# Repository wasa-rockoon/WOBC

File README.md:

View this project on [CADLAB.io](https://cadlab.io/project/27502). 

# WOBC

WOBCは，WASAロケットプロジェクトにおける電装関連の共通基盤を確立することを目的としたプロジェクトである．
開発した回路や基板の設計情報，プログラムといった資産を再利用しやすい形で整備することで，
開発スピードを向上させるとともに引き継ぎや教育を効率的に行えるようにする．

# 用語

## ユニット

単独で動作する，システムの基本単位．例：ロケット電装，CanSat電装，地上局

1つ以上のモジュールから構成される．

## モジュール

コンポーネントを一枚の基板上に配置した，物理的な単位．例：地上局モジュール，通信モジュール

モジュールには必ずマイコンが含まれ，コンポーネントを制御する．
ユニットを構成するモジュール間はバスで接続される．

## コンポーネント

ユニットを構成する，意味のある一つの機能単位．例：電源管理，姿勢決定，モーター駆動

ハードウェアおよびプログラムはコンポーネント単位で開発する．

## パケット

ユニットやコンポーネント間でやり取りするデータの形式．
詳しくは[WCPP](https://github.com/wasa-rockoon/WCPP)を参照．

# 開発

モジュールやコンポーネントは，全てこのリポジトリに格納する（Monorepoスタイル）．

## Gitの運用

- 開発者ごとに，`develop/your_name` ブランチを作成する．
- 全体に反映したい変更ができたらPull Requestを作成し，責任者にレビューを依頼する．
- コンポーネントおよびモジュール作成の際は自分のブランチとは別に，`feature/CompornentOrModule_name`ブランチを作成する．
- コンポーネント・モジュールが完成したらPull Requestを作成し，責任者にレビューを依頼する．
- 責任者は変更をレビューし，問題なければ`main`ブランチにマージする．（回路・基板のレビューには[CADLAB.io](https://cadlab.io/project/27502)を使うと便利)

## Github Copilotの学生無料

昨今コーディング作業に`AI Agent`の活用が主流になってきていると思います．ただ無料枠で利用していてもすぐトークンを使い切ってしまったり，選べるモデルが少なかったりと不便なことが多いかと思います．そこで個人的にはGithub Copilotの学生無料を利用することを推奨しています．導入方法については`ドキュメント`にあるリンクから参照してください．

## 作業ログ

`Github Copilot`の利用にあわせて，作業ログを作ることを習慣化してほしいと思います．おもにコーディング作業についてですが，

- 前にも同じようなエラーが出てたけど，どうやって解消したんだっけとか
- 過去にも似たようなもの作ってたらしいけど，資料が残っていないとか

色々と引継ぎが上手くいっていないような事象を見かけます．非常にもったいないというか二度手間なことが多いので，ちゃんとノウハウを蓄積できるようにしましょう．

具体的には `docs`のフォルダに`env:`毎でフォルダを作りその中で[template](docs/template.md)を参考にしてAIに作らせてください．タスク毎に作るのが良いかと思います．

# ドキュメント

- [develop](docs/develop.md): 詳細な開発の手順
- [kicad](docs/kicad.md): KiCADを用いた回路・基板設計マニュアル
- [github-copilot](docs/github-copilot.md): Github Copilotの導入マニュアル
- [components](docs/components.md): コンポーネントとその機能，インターフェースの一覧
- [modules](docs/modules.md): モジュールとその機能，構成コンポーネントの一覧
- [unit](docs/unit.md): ユニット一覧
- [library](docs/library.md): WOBCライブラリの使い方

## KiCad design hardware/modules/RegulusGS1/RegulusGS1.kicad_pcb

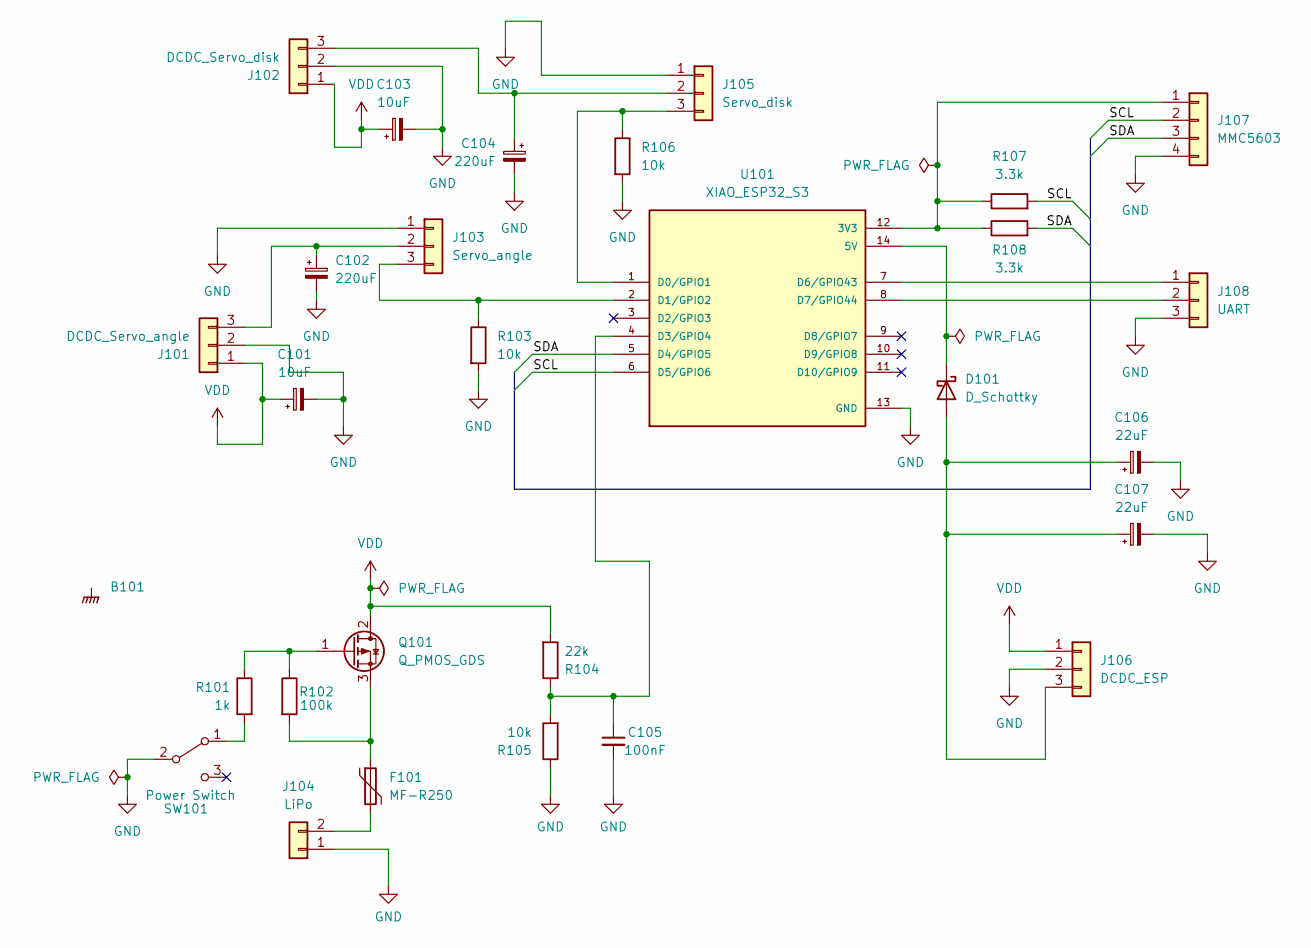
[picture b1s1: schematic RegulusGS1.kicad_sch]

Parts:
B101: Board_1U_60x60
C101, C103: 10uF; CP_Radial_D5.0mm_P2.50mm
C102, C104: 220uF; CP_Radial_D8.0mm_P5.00mm
C105: 100nF; C_Disc_D3.0mm_W2.0mm_P2.50mm
C106, C107: 22uF; CP_Radial_D5.0mm_P2.50mm
D101: D_Schottky; D_DO-41_SOD81_P10.16mm_Horizontal
F101: MF-R250; Fuse_Bourns_MF-R250_1
J101: DCDC_Servo_angle; PinHeader_1x03_P2.54mm_Horizontal
J102: DCDC_Servo_disk; PinHeader_1x03_P2.54mm_Horizontal
J103: Servo_angle; JST_XH_B3B-XH-A_1x03_P2.50mm_Vertical
J104: LiPo; AMASS_XT30PW-M_1x02_P2.50mm_Horizontal
J105: Servo_disk; JST_XH_B3B-XH-A_1x03_P2.50mm_Vertical
J106: DCDC_ESP; PinHeader_1x03_P2.54mm_Vertical
J107: MMC5603; PinHeader_1x04_P2.54mm_Vertical
J108: UART; JST_XH_B3B-XH-A_1x03_P2.50mm_Vertical
Q101: Q_PMOS_GDS; TO-220-3_Vertical
R101: 1k; R_Axial_DIN0207_L6.3mm_D2.5mm_P7.62mm_Horizontal
R102: 100k; R_Axial_DIN0207_L6.3mm_D2.5mm_P7.62mm_Horizontal
R103, R105, R106: 10k; R_Axial_DIN0207_L6.3mm_D2.5mm_P7.62mm_Horizontal
R104: 22k; R_Axial_DIN0207_L6.3mm_D2.5mm_P7.62mm_Horizontal
R107, R108: 3.3k; R_Axial_DIN0207_L6.3mm_D2.5mm_P7.62mm_Horizontal
SW101: Power Switch; SW_Slide_SPDT_Angled_CK_OS102011MA1Q
U101: XIAO_ESP32_S3; MODULE_XIAO_ESP32_S3; PARTREV April 22nd, 2026

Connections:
/SCL: J107.2, R107.2, U101.6 (D5/GPIO6)
/SDA: J107.3, R108.2, U101.5 (D4/GPIO5)
GND: B101.GND, C101.2, C102.2, C103.2, C104.2, C105.2, C106.2, C107.2, J101.2, J102.2, J103.1, J104.1, J105.1, J106.2, J107.4, J108.3, R103.2, R105.1, R106.2, SW101.2 (B), U101.13 (GND)
unnamed: C106.1, C107.1, D101.2 (A), J106.3
unnamed: D101.1 (K), U101.14 (5V)
unnamed: C102.1, J101.3, J103.2
unnamed: C104.1, J102.3, J105.2
unnamed: J103.3, R103.1, U101.2 (D1/GPIO2)
unnamed: F101.2, J104.2
unnamed: J105.3, R106.1, U101.1 (D0/GPIO1)
unnamed: J107.1, R107.1, R108.1, U101.12 (3V3)
unnamed: J108.1, U101.7 (D6/GPIO43)
unnamed: J108.2, U101.8 (D7/GPIO44)
unnamed: Q101.1 (G), R101.1, R102.1
unnamed: F101.1, Q101.3 (S), R102.2
unnamed: R101.2, SW101.1 (A)
unnamed: C105.1, R104.1, R105.2, U101.4 (D3/GPIO4)
VDD: C101.1, C103.1, J101.1, J102.1, J106.1, Q101.2 (D), R104.2

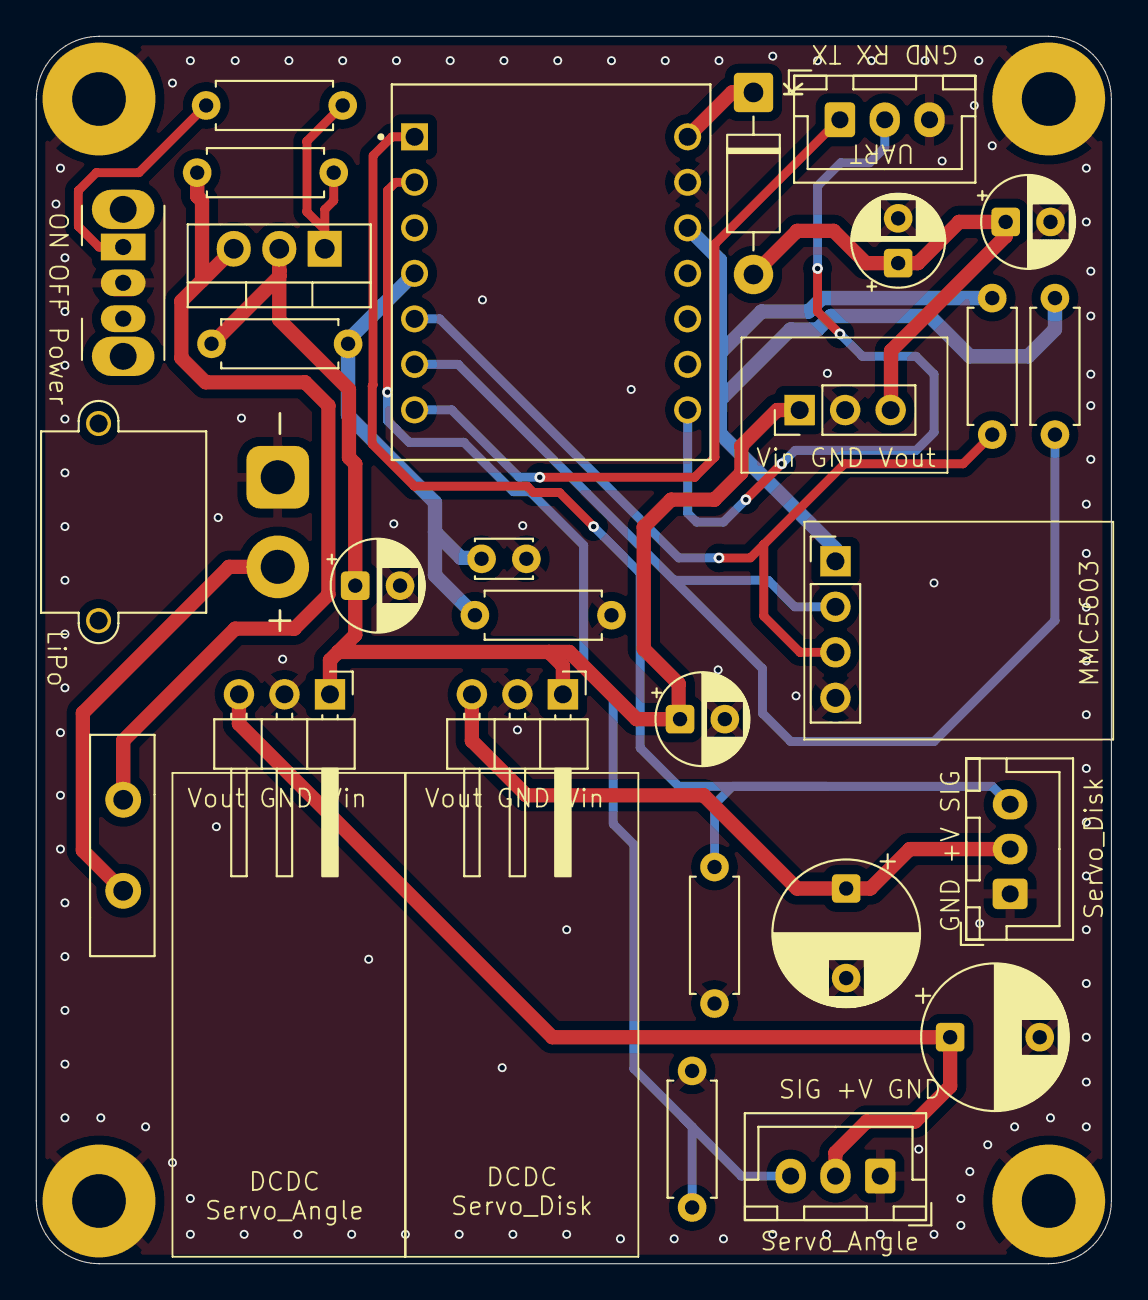
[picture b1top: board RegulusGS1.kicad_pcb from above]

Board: 2 copper layers, 60.0 x 68.5 mm, 29 parts (0 on the bottom side), 18 nets.

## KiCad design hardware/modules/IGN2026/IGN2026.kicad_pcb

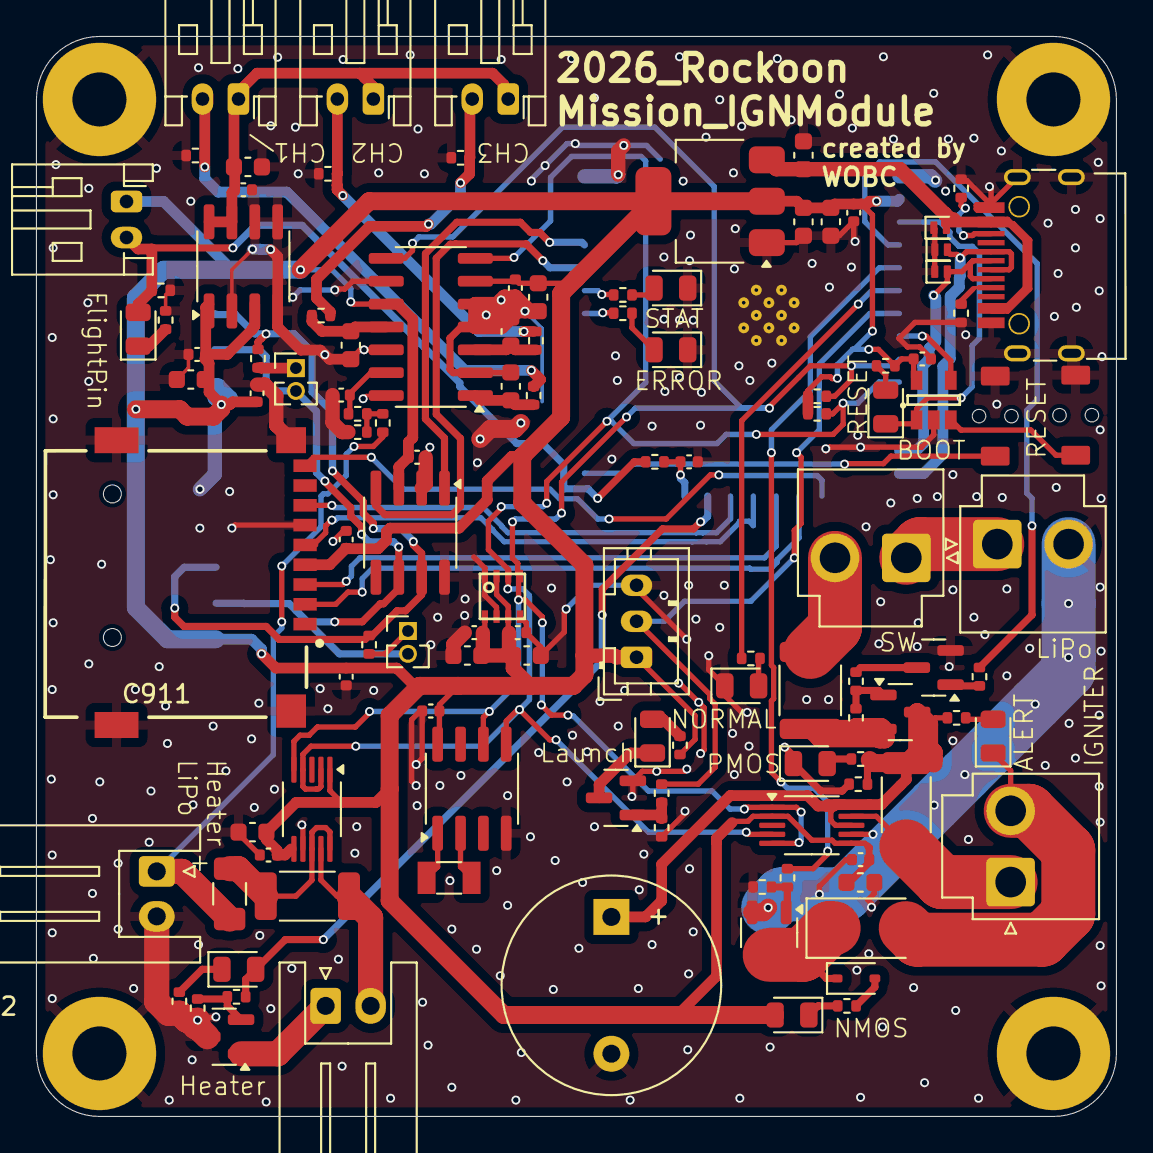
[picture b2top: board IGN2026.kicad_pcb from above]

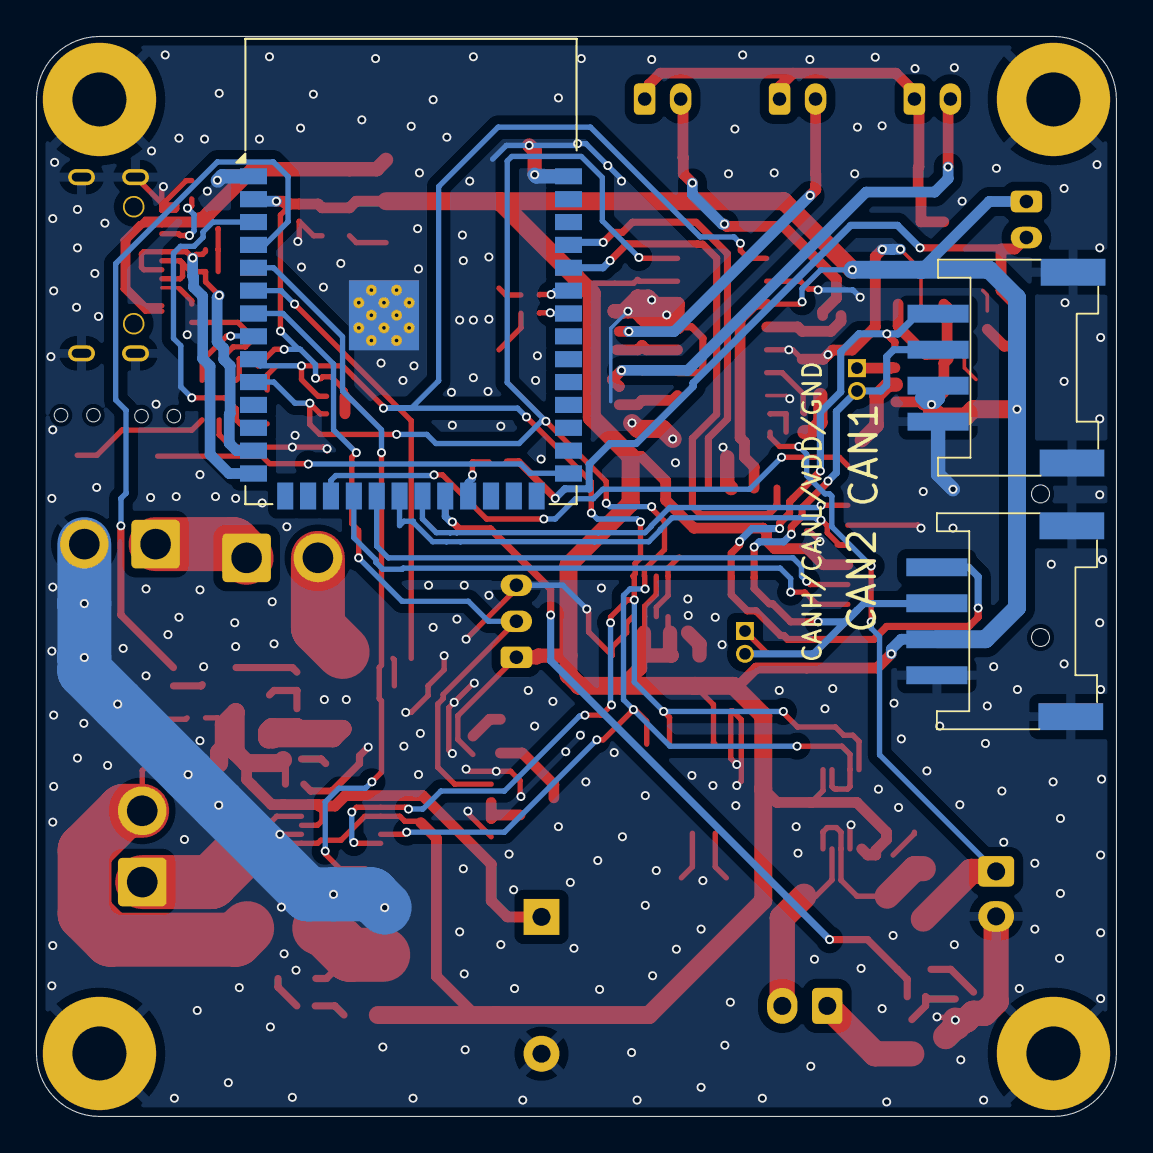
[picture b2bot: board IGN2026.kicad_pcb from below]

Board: 2 copper layers, 60.0 x 60.0 mm, 121 parts (3 on the bottom side), 73 nets.

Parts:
B101: Board_1U_60x60
BZ801: Buzzer; Buzzer_12x9.5RM7.6
C101, C102, C201, C801, C901, C903, C905, C906, C907, C908, C912: 10uF; C_0603_1608Metric
C202, C203, C204, C301, C401, C501, C602, C603, C802: 100nF; C_0402_1005Metric
C302: 10uF; C_0402_1005Metric
C601, C604: 10μF; C_0603_1608Metric
C701, C902, C904, C909, C910, C911: 100n; C_0402_1005Metric
D201, D202, D203: 5V; D_SOD-882
D204: ERROR; LED_0805_2012Metric
D205: STAT; LED_0805_2012Metric
D206: RESET; LED_0805_2012Metric
D701: Flightpin; LED_0805_2012Metric
D801: PMOS; LED_0805_2012Metric
D802: NORMAL; LED_0805_2012Metric
D803: ALERT; LED_0805_2012Metric
D804: D_Schottky; D_SMA
D805: D_Schottky; D_SOD-323
D806: NMOS; LED_0805_2012Metric
D807: LaunchDetection; LED_0805_2012Metric
F801: Polyfuse; Fuse_1812_4532Metric
F901: Polyfuse; Fuse_1206_3216Metric
J401, J501: Jumper; PinHeader_1x02_P1.27mm_Vertical
J402, J502: Conn_01x04_MountingPin; Grove_4P_L_SMD
J701: Flightpin; JST_PH_S2B-PH-K_1x02_P2.00mm_Horizontal
J801: LiPo 3 Cell; JST_VH_B2P-VH_1x02_P3.96mm_Vertical
J802: PowerSW; JST_VH_B2P-VH_1x02_P3.96mm_Vertical
J803: IGNITER; JST_VH_B2P-VH_1x02_P3.96mm_Vertical
J804: LaunchDetection; JST_PH_B3B-PH-K_1x03_P2.00mm_Vertical
J901: HeaterLiPo; JST_XH_S2B-XH-A_1x02_P2.50mm_Horizontal
J902: THR1; JST_PH_S2B-PH-K_1x02_P2.00mm_Horizontal
J903: THR2; JST_PH_S2B-PH-K_1x02_P2.00mm_Horizontal
J904: Heater; JST_XH_S2B-XH-A_1x02_P2.50mm_Horizontal
J905: THR3; JST_PH_S2B-PH-K_1x02_P2.00mm_Horizontal
LED901: Heater; LED_0805_2012Metric
MICRO_SD301: TF-01A
Q801: Q_PMOS_GSD; SOT-23
Q802: Q_NPN_BEC; SOT-23
Q803: Q_NMOS_DGS; SOT-23-3
Q804, Q901: NMOS; SOT-23
R201, R202: 5.1k; R_0402_1005Metric
R203, R207, R701, R801, R806, R812, R814, R902, R905, R907, R909, R913: 10k; R_0402_1005Metric
R204, R205, R206: 470; R_0402_1005Metric
R401, R501, R901, R904, R908: 120; R_0402_1005Metric
R702, R703, R803, R804, R805, R808, R809, R810, R910, R912: 1k; R_0402_1005Metric
R802: 3.3k; R_0402_1005Metric
R807, R903: 20mΩ; R_2010_5025Metric
R811, R813, R906: 510; R_0402_1005Metric
R911: 47k; R_0402_1005Metric
SW201: Boot_sw; TVAF06-A020B-R
SW202: RESET_sw; TVAF06-A020B-R
U101: AMS1117-3.3; SOT-223-3_TabPin2
U201: ESP32-S3-WROOM-1
U202: TPS3820; SOT_23_5
U203: SN65HVD230; SOIC-8_3.9x4.9mm_P1.27mm
U301: PCF8563T; SOIC-8_3.9x4.9mm_P1.27mm
U601: BME280
U801, U901: INA226; VSSOP-10_3x3mm_P0.5mm
U902: MCP3424x-xSL; SOIC-14_3.9x8.7mm_P1.27mm
U904: MCP1501-20xSN; SOIC-8_3.9x4.9mm_P1.27mm
USB201: USB_C_Receptacle_USB2.0; USB_C_TYPEC-301S-ACP16X7
Y301: Crystal; Crystal_SMD_3215-2Pin_3.2x1.5mm

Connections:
/CANH: J402.1, J502.1, R401.2, R501.2, U203.7 (CANH)
/CANL: J401.2, J402.2, J501.2, J502.2, U203.6 (CANL)
/CS: MICRO_SD301.2 (CD/DAT3), U201.18 (GPIO10/TOUCH10/ADC1_CH9/FSPICS0/FSPIIO4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)
/DET: MICRO_SD301.CD1 (CD), U201.17 (GPIO9/TOUCH9/ADC1_CH8/FSPIHD/SUBSPIHD)
/ESP32core/CAN_RX: U201.36 (U0RXD/GPIO44/CLK_OUT2), U203.4 (R)
/ESP32core/CAN_TX: U201.37 (U0TXD/GPIO43/CLK_OUT1), U203.1 (D)
/ESP32core/GPIO6/ADC1_CH5: R805.1, U201.6 (GPIO6/TOUCH6/ADC1_CH5)
/ESP32core/GPIO14: LED901.2 (A), R906.2, U201.22 (GPIO14/TOUCH14/ADC2_CH3/FSPIWP/FSPIDQS/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)
/ESP32core/GPIO21: C701.1, R703.1, U201.23 (GPIO21)
/ESP32core/USB_D+: D202.2 (A2), U201.14 (GPIO20/U1CTS/ADC2_CH9/CLK_OUT1/USB_D+), USB201.A6 (D+), USB201.B6 (D+)
/ESP32core/USB_D-: D203.2 (A2), U201.13 (GPIO19/U1RTS/ADC2_CH8/CLK_OUT2/USB_D-), USB201.A7 (D-), USB201.B7 (D-)
/ESP32core/WDI: U201.8 (GPIO15/U0RTS/ADC2_CH4/XTAL_32K_P), U202.4 (WDI)
/Heater/CH1: C905.1, R901.1, U902.1 (CH1+)
/Heater/CH2: C906.1, R904.1, U902.3 (CH2+)
/Heater/CH3: C907.1, R908.1, U902.11 (CH3+)
/Heater/CH4: C910.1, R912.1, U902.13 (CH4+)
/Heater/VPPheater: F901.2, J901.1, R911.1
/Heater/Vref: C911.2, C912.2, J902.1, J903.1, J905.1, U904.7 (OUT), U904.8 (FB)
/I2C_SCL: R203.2, U201.9 (GPIO16/U0CTS/ADC2_CH5/XTAL_32K_N), U301.6 (SCL), U601.4 (SCK), U801.1 (A1), U801.5 (SCL), U901.5 (SCL), U902.8 (SCL)
/I2C_SDA: R207.2, U201.10 (GPIO17/U1TXD/ADC2_CH6), U301.5 (SDA), U601.3 (SDI), U801.4 (SDA), U901.2 (A0), U901.4 (SDA), U902.7 (SDA)
/Ignite/IGNITE+: R803.1, U201.4 (GPIO4/TOUCH4/ADC1_CH3)
/Ignite/IGNITE-: R811.1, U201.5 (GPIO5/TOUCH5/ADC1_CH4)
/Ignite/Ldet: J804.2, R813.2, U201.7 (GPIO7/TOUCH7/ADC1_CH6)
/MISO: MICRO_SD301.7 (DAT0), U201.21 (GPIO13/TOUCH13/ADC2_CH2/FSPIQ/FSPIIO7/S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)
/MOSI: MICRO_SD301.3 (CMD), U201.19 (GPIO11/TOUCH11/ADC2_CH0/FSPID/FSPIIO5/S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)
/SCK: MICRO_SD301.5 (CLK), U201.20 (GPIO12/TOUCH12/ADC2_CH1/FSPICLK/FSPIIO6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)
GND: B101.GND, BZ801.2 (-), C101.2, C102.2, C201.1, C202.2, C203.1, C204.1, C301.1, C302.2, C401.1, C501.1, C601.2, C602.2, C603.2, C604.2, C701.2, C801.2, C802.2, C901.2, C902.2, C903.2, C904.2, C905.2, C906.2, C907.2, C908.2, C909.2, C910.2, C911.1, C912.1, D201.1 (A1), D202.1 (A1), D203.1 (A1), D204.1 (K), D205.1 (K), D801.1 (K), D802.1 (K), J402.4, J402.MP (MountPin), J502.4, J502.MP (MountPin), J801.2, J804.3, J901.2, MICRO_SD301.6 (VSS), MICRO_SD301.MP1 (SHIELD), MICRO_SD301.MP2 (SHIELD), MICRO_SD301.MP3 (SHIELD), MICRO_SD301.MP4 (SHIELD), Q802.2 (E), Q803.2 (S), Q804.2 (S), Q901.3 (S), R201.2, R202.2, R701.2, R702.2, R806.1, R812.1, R814.2, R902.2, R905.2, R907.2, R909.2, R910.2, R913.2, SW201.2, SW202.2, U101.1 (GND), U201.1 (GND), U201.40 (GND), U201.41 (GND), U202.2 (GND), U203.2 (GND), U203.8 (Rs), U301.4 (VSS), U601.1 (GND), U601.5 (SDO), U601.7 (GND), U801.7 (GND), U901.7 (GND), U902.2 (CH1-), U902.4 (CH2-), U902.5 (V_{SS}), U902.9 (A0), U902.12 (CH3-), U902.14 (CH4-), U904.2 (GND), U904.4 (GND), U904.5 (GND), U904.6 (GND), USB201.A1 (GND), USB201.A12 (GND), USB201.B1 (GND), USB201.B12 (GND), USB201.S1 (SHIELD)
unnamed: BZ801.1 (+), Q801.3 (D), R804.1, R806.2, R807.2, R808.1, U801.8 (Vbus), U801.10 (Vin+)
unnamed: D204.2 (A), R204.2
unnamed: D205.2 (A), R205.2
unnamed: D206.2 (A), R206.2
unnamed: D701.2 (A), J701.2, R701.1, R703.2
unnamed: D701.1 (K), R702.1
unnamed: D801.2 (A), R804.2
unnamed: D802.2 (A), R805.2
unnamed: D803.2 (A), R808.2
unnamed: D803.1 (K), D804.2 (A), J803.2 (Pin_1)
unnamed: D804.1 (K), D805.1 (K), Q803.3 (D)
unnamed: D805.2 (A), R809.2
unnamed: D806.1 (K), R809.1
unnamed: D807.2 (A), R810.2
unnamed: D807.1 (K), Q804.3 (D)
unnamed: J401.1, R401.1
unnamed: J501.1, R501.1
unnamed: J801.1, J802.1
unnamed: F801.1, J802.2
unnamed: J803.1 (Pin_2), R807.1, U801.9 (Vin-)
unnamed: J902.2, R901.2, R902.1
unnamed: J903.2, R904.2, R905.1
unnamed: J904.2 (Pin_1), R903.1, U901.9 (Vin-)
unnamed: J904.1 (Pin_2), Q901.1 (D)
unnamed: J905.2, R908.2, R909.1
unnamed: LED901.1 (K), R910.1
unnamed: Q801.1 (G), R801.2, R802.1
unnamed: F801.2, Q801.2 (S), R801.1
unnamed: Q802.1 (B), R803.2
unnamed: Q802.3 (C), R802.2
unnamed: Q803.1 (G), R811.2, R812.2
unnamed: Q804.1 (G), R813.1, R814.1
unnamed: Q901.2 (G), R906.1, R907.1
unnamed: R911.2, R912.2, R913.1
unnamed: SW201.1, U201.27 (GPIO0/BOOT)
unnamed: R204.1, U201.34 (MTDI/GPIO41/CLK_OUT1)
unnamed: R205.1, U201.35 (MTMS/GPIO42)
unnamed: SW202.1, U202.3 (MR)
unnamed: U301.1 (OSCI), Y301.1
unnamed: U301.2 (OSCO), Y301.2
unnamed: F901.1, R903.2, U901.8 (Vbus), U901.10 (Vin+)
unnamed: R201.1, USB201.A5 (CC1)
unnamed: R202.1, USB201.B5 (CC2)
RESET: D206.1 (K), U201.3 (EN), U202.1 (RESET)
VBUS: C102.1, D201.2 (A2), U101.3 (VI), USB201.A4 (VBUS), USB201.A9 (VBUS), USB201.B4 (VBUS), USB201.B9 (VBUS)
VDD: C101.1, C201.2, C202.1, C203.2, C204.2, C301.2, C302.1, C401.2, C501.2, C601.1, C602.1, C603.1, C604.1, C801.1, C802.1, C901.1, C902.1, C903.1, C904.1, C908.1, C909.1, D806.2 (A), J402.3, J502.3, J701.1, J804.1, MICRO_SD301.4 (VDD), R203.1, R206.1, R207.1, R810.1, U101.2 (VO), U201.2 (3V3), U202.5 (VDD), U203.3 (VCC), U301.8 (VDD), U601.2 (CSB), U601.6 (VDDIO), U601.8 (VDD), U801.2 (A0), U801.6 (VS), U901.1 (A1), U901.6 (VS), U902.6 (V_{DD}), U902.10 (A1), U904.1 (VDD), U904.3 (~SHDN)

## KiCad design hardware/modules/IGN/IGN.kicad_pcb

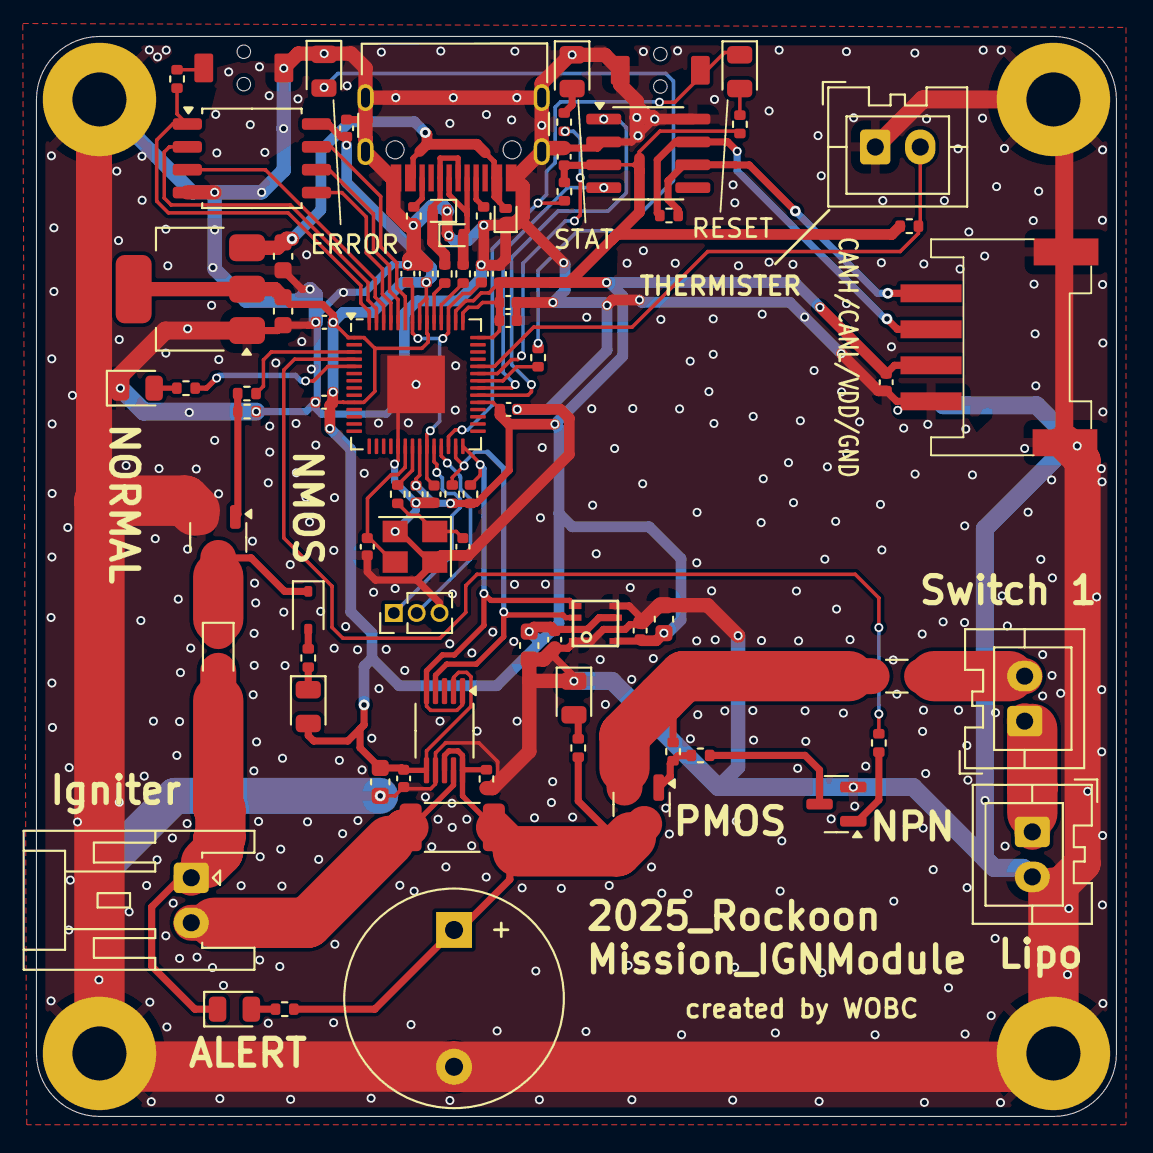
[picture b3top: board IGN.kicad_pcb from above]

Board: 2 copper layers, 60.0 x 60.0 mm, 82 parts (0 on the bottom side), 54 nets.

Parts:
BZ201: Buzzer; Buzzer_12x9.5RM7.6
C101, C102, C201: 10uF; C_0603_1608Metric
C202, C301, C302, C305, C306, C308, C310, C311, C312, C313, C314, C315, C401, C502, C503: 100nF; C_0402_1005Metric
C303, C304: 27pF; C_0402_1005Metric
C307, C309: 1uF; C_0402_1005Metric
C501, C504: 10μF; C_0603_1608Metric
D201: PMOS; LED_0805_2012Metric
D202, D204: D_Schottky; D_SOD-323
D203: ALERT; LED_0805_2012Metric
D205: NMOS; LED_0805_2012Metric
D206: NORMAL; LED_0805_2012Metric
D301: RESET; LED_0805_2012Metric
D302, D303, D304: 5V; D_SOD-882D
D305: STAT; LED_0805_2012Metric
D306: ERROR; LED_0805_2012Metric
F201: Polyfuse; Fuse_1206_3216Metric
J101: THERMISTER; JST_XA_B02B-XASK-1_1x02_P2.50mm_Vertical
J201: LiPo 2 Cell; JST_XA_B02B-XASK-1_1x02_P2.50mm_Vertical
J202: IGNITER; JST_XA_S02B-XASK-1N-BN_1x02_P2.50mm_Horizontal
J203: PowerSW; JST_XA_B02B-XASK-1_1x02_P2.50mm_Vertical
J301: DEBUG; PinHeader_1x03_P1.27mm_Vertical
J402: Conn_01x04_MountingPin; Grove_4P_L_SMD
Q201: Q_PMOS_GSD; SOT-23
Q202: Q_NMOS_DGS; SOT-23-3
Q203: Q_NPN_BEC; SOT-23
R101, R202, R204, R205, R301, R309, R311: 10k; R_0402_1005Metric
R201, R207, R209, R210, R211, R302, R305, R308, R310, R312: 1k; R_0402_1005Metric
R203: 20mΩ; R_2010_5025Metric
R206, R208: 510; R_0402_1005Metric
R303, R304: 5.1k; R_0402_1005Metric
R306, R307: 22.4; R_0402_1005Metric
R401: 120; R_0402_1005Metric
SW301: RESET_sw; TVAF06-A020B-R
SW302: BOOT0; TVAF06-A020B-R
U101: AMS1117-3.3; SOT-223-3_TabPin2
U201: INA226; VSSOP-10_3x3mm_P0.5mm
U301: SN65HVD230; SOIC-8_3.9x4.9mm_P1.27mm
U302: W25Q128JVS; SOIC-8_5.3x5.3mm_P1.27mm
U303: RP2040; QFN-56-1EP_7x7mm_P0.4mm_EP3.2x3.2mm
U501: BME280
USB301: USB_C_Receptacle_USB2.0; USB_C_TYPEC-301S-ACP16X7
Y301: Crystal_GND24; Crystal_SMD_3225-4Pin_3.2x2.5mm

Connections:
/HIGH: R210.1, U303.4 (GPIO2)
/I2C_SCL: R311.2, U201.1 (A1), U201.5 (SCL), U303.28 (GPIO17), U501.4 (SCK)
/I2C_SDA: R309.2, U201.4 (SDA), U303.27 (GPIO16), U501.3 (SDI)
/IF/CANH: J402.1, R401.2, U301.6 (CANL)
/IF/CANL: J402.2, R401.1, U301.7 (CANH)
/LOW: R208.1, U303.3 (GPIO1)
/Normal: R211.1, U303.5 (GPIO3)
/RP2040core/CAN_RX: U301.4 (R), U303.35 (GPIO23)
/RP2040core/CAN_TX: U301.1 (D), U303.34 (GPIO22)
/RP2040core/GPIO26_ADC0: J101.2, R101.2, U303.38 (GPIO26_ADC0)
/RP2040core/USB_D+: D303.2 (A2), R306.1, USB301.A6 (D+), USB301.B6 (D+)
/RP2040core/USB_D-: D304.2 (A2), R307.1, USB301.A7 (D-), USB301.B7 (D-)
GND: BZ201.2 (-), C101.2, C102.2, C201.2, C202.2, C301.1, C302.1, C303.1, C304.1, C305.2, C306.2, C307.1, C308.2, C309.1, C310.2, C311.2, C312.2, C313.2, C314.2, C315.2, C401.1, C501.2, C502.2, C503.2, C504.2, D201.1 (K), D206.1 (K), D302.1 (A1), D303.1 (A1), D304.1 (A1), D305.1 (K), D306.1 (K), J101.1, J201.2, J301.3, J402.4, J402.MP (MountPin), Q202.2 (S), Q203.2 (E), R202.1, R205.1, R303.2, R304.2, SW301.2, SW302.1, U101.1 (GND), U201.7 (GND), U301.2 (GND), U301.8 (Rs), U302.4 (GND), U303.19 (TESTEN), U303.57 (GND), U501.1 (GND), U501.5 (SDO), U501.7 (GND), USB301.A1 (GND), USB301.A12 (GND), USB301.B1 (GND), USB301.B12 (GND), USB301.S1 (SHIELD), Y301.2, Y301.4
unnamed: BZ201.1 (+), Q201.3 (D), R201.1, R202.2, R203.2, R207.1, U201.8 (Vbus), U201.10 (Vin+)
unnamed: C304.2, R308.1, Y301.1
unnamed: D201.2 (A), R201.2
unnamed: D202.2 (A), D203.1 (K), J202.1
unnamed: D202.1 (K), D204.1 (K), Q202.3 (D)
unnamed: D203.2 (A), R207.2
unnamed: D204.2 (A), R209.2
unnamed: D205.1 (K), R209.1
unnamed: D206.2 (A), R211.2
unnamed: D301.2 (A), R302.2
unnamed: D305.2 (A), R310.2
unnamed: D306.2 (A), R312.2
unnamed: J201.1, J203.1
unnamed: J202.2, R203.1, U201.9 (Vin-)
unnamed: F201.1, J203.2
unnamed: J301.1, U303.24 (SWCLK)
unnamed: J301.2, U303.25 (SWD)
unnamed: Q201.1 (G), R204.2, R206.1
unnamed: F201.2, Q201.2 (S), R204.1
unnamed: Q202.1 (G), R205.2, R208.2
unnamed: Q203.1 (B), R210.2
unnamed: Q203.3 (C), R206.2
unnamed: R305.2, SW302.2
unnamed: U302.6 (CLK), U303.52 (QSPI_SCLK)
unnamed: U302.5 (DI(IO0)), U303.53 (QSPI_SD0)
unnamed: U302.2 (DO(IO1)), U303.55 (QSPI_SD1)
unnamed: U302.3 (IO2), U303.54 (QSPI_SD2)
unnamed: U302.7 (IO3), U303.51 (QSPI_SD3)
unnamed: R305.1, U302.1 (~CS), U303.56 (QSPI_SS)
unnamed: R312.1, U303.36 (GPIO24)
unnamed: R310.1, U303.37 (GPIO25)
unnamed: R307.2, U303.46 (USB_DM)
unnamed: R306.2, U303.47 (USB_DP)
unnamed: C305.1, C306.1, C307.2, U303.23 (DVDD), U303.45 (VREG_VOUT), U303.50 (DVDD)
unnamed: C303.2, U303.20 (XIN), Y301.3
unnamed: R308.2, U303.21 (XOUT)
unnamed: R303.1, USB301.A5 (CC1)
unnamed: R304.1, USB301.B5 (CC2)
RESET: D301.1 (K), R301.2, SW301.1, U303.26 (RUN)
VBUS: C101.1, D302.2 (A2), U101.3 (VI), USB301.A4 (VBUS), USB301.A9 (VBUS), USB301.B4 (VBUS), USB301.B9 (VBUS)
VDD: C102.1, C201.1, C202.1, C301.2, C302.2, C308.1, C309.2, C310.1, C311.1, C312.1, C313.1, C314.1, C315.1, C401.2, C501.1, C502.1, C503.1, C504.1, D205.2 (A), J402.3, R101.1, R301.1, R302.1, R309.1, R311.1, U101.2 (VO), U201.2 (A0), U201.6 (VS), U301.3 (VCC), U302.8 (VCC), U303.1 (IOVDD), U303.10 (IOVDD), U303.22 (IOVDD), U303.33 (IOVDD), U303.42 (IOVDD), U303.43 (ADC_AVDD), U303.44 (VREG_IN), U303.48 (USB_VDD), U303.49 (IOVDD), U501.2 (CSB), U501.6 (VDDIO), U501.8 (VDD)

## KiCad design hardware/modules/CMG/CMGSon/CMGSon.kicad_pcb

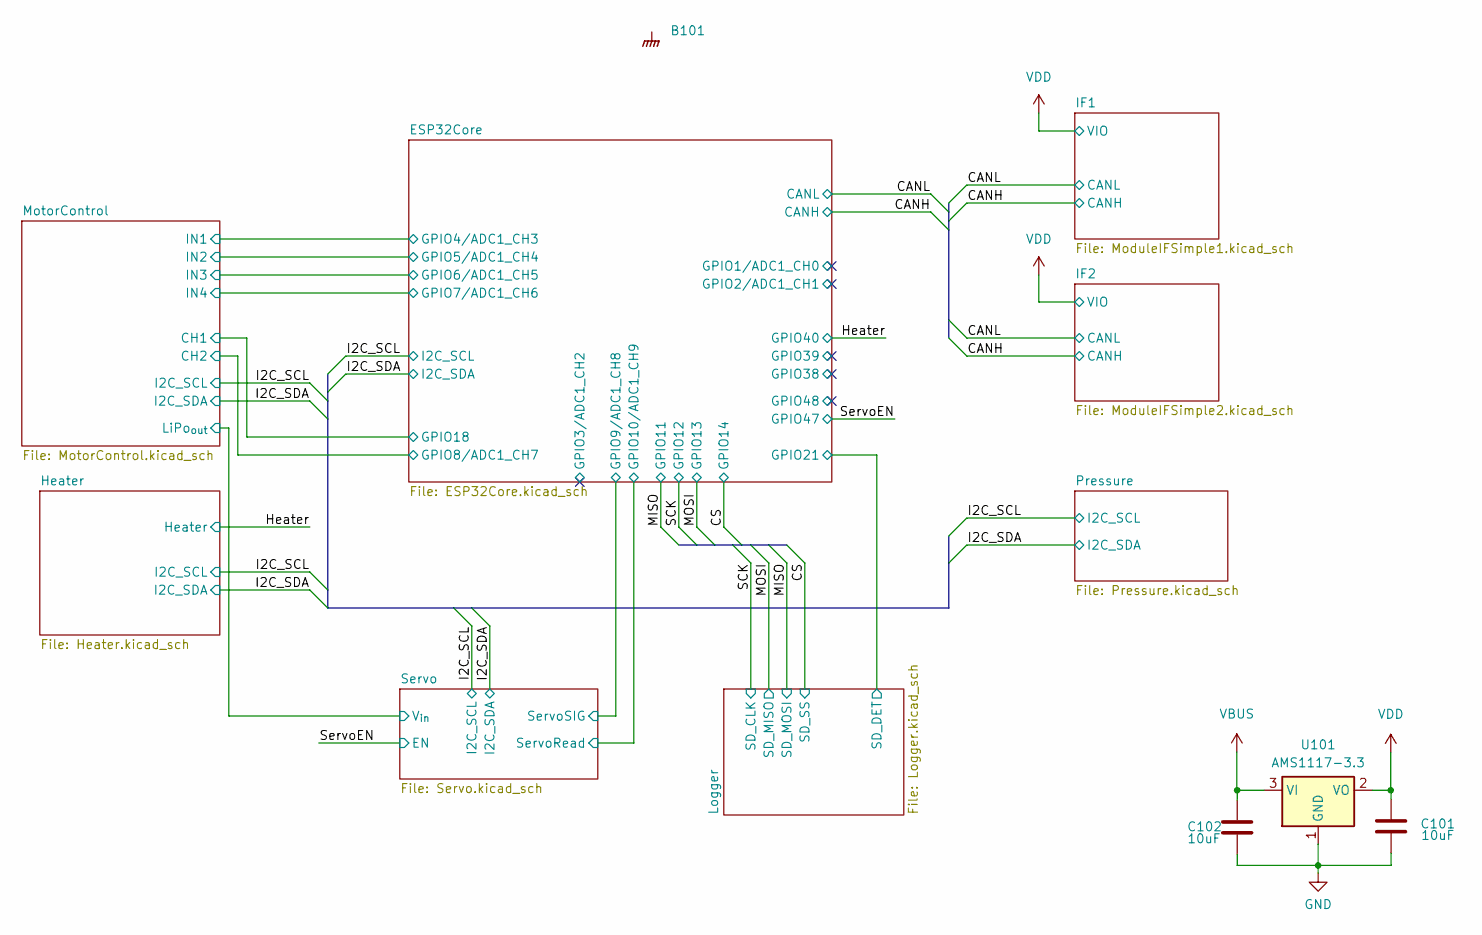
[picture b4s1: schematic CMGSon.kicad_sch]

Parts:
B101: Board_1U_60x60
C101, C102: 10uF; C_0603_1608Metric; LCSC C96446
U101: AMS1117-3.3; SOT-223-3_TabPin2; LCSC C6186

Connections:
GND: B101.GND, C101.2, C102.2, U101.1 (GND); also elsewhere on the board
VBUS: C102.1, U101.3 (VI); also elsewhere on the board
VDD: C101.1, U101.2 (VO); also elsewhere on the board

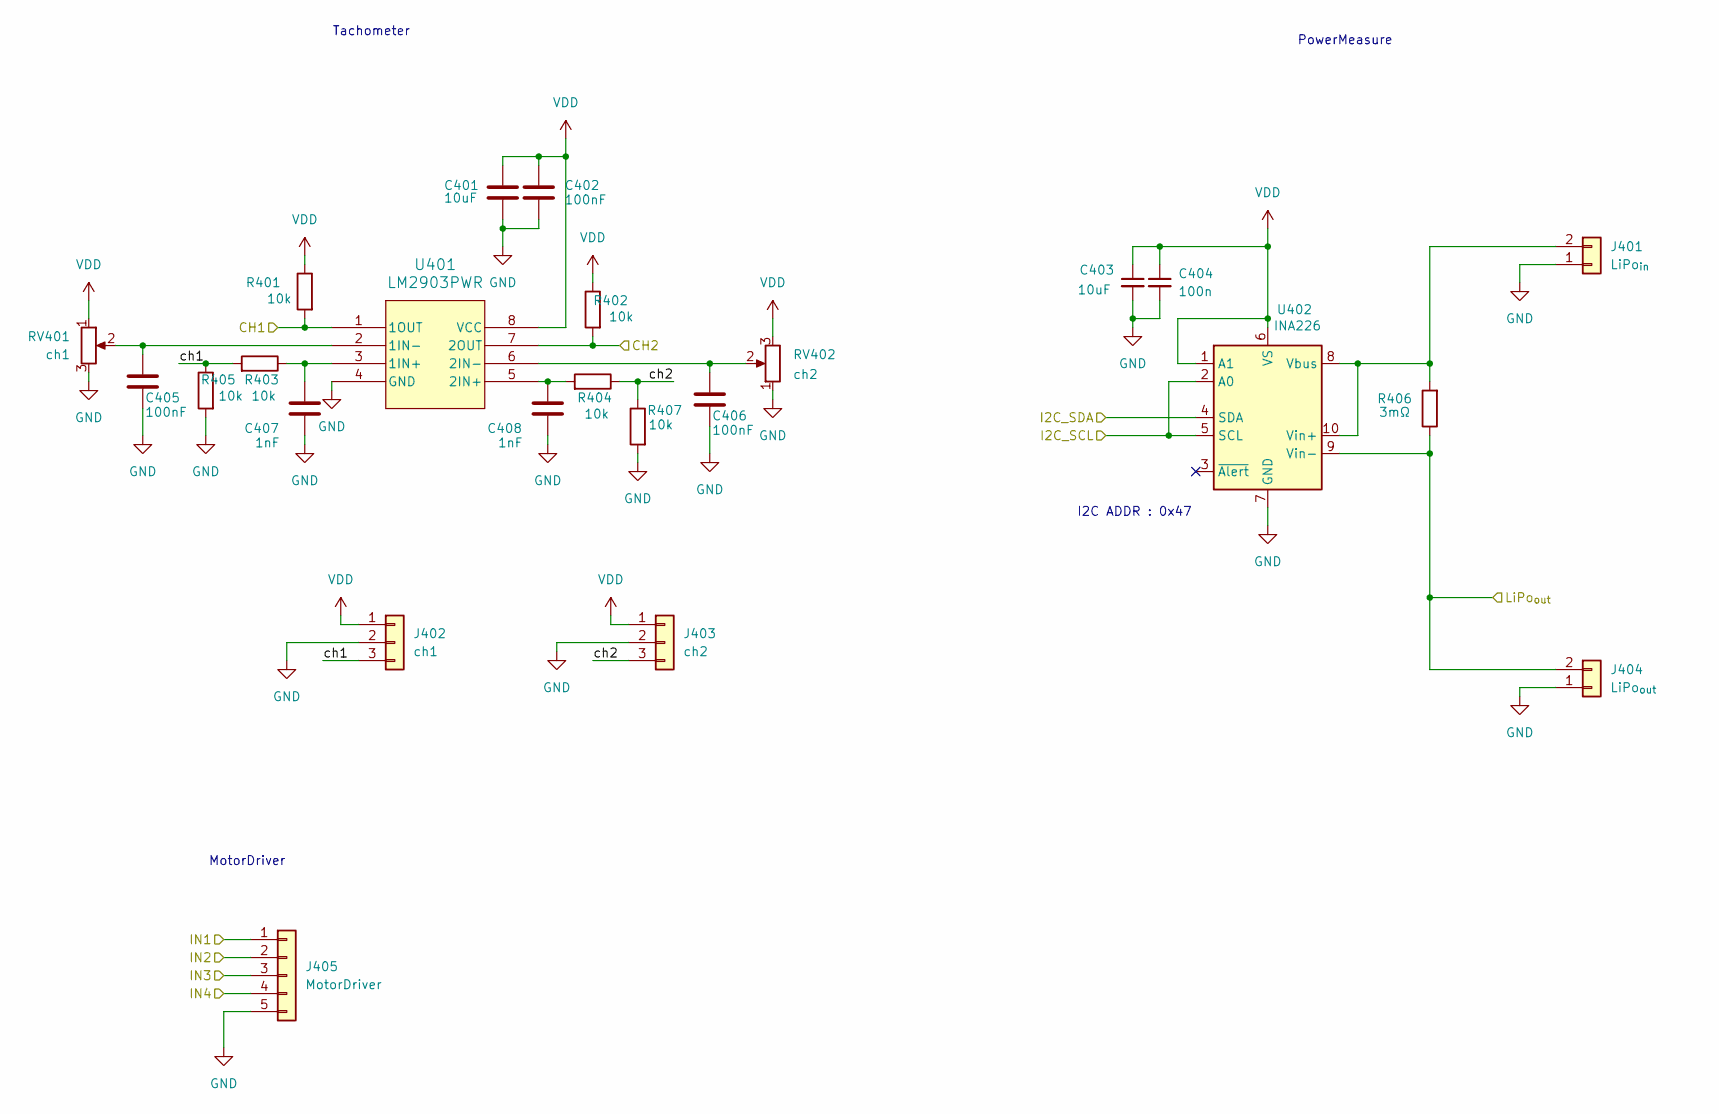
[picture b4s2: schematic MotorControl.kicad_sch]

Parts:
C401, C403: 10uF; C_0603_1608Metric; LCSC C19702
C402, C405, C406: 100nF; C_0402_1005Metric; LCSC C1525
C404: 100n; C_0402_1005Metric; LCSC C1525
C407, C408: 1nF; C_0402_1005Metric; LCSC C1523
J401: LiPo_{in}; AMASS_XT30PW-M_1x02_P2.50mm_Horizontal
J402: ch1; JST_PH_B3B-PH-K_1x03_P2.00mm_Vertical
J403: ch2; JST_PH_B3B-PH-K_1x03_P2.00mm_Vertical
J404: LiPo_{out}; AMASS_XT30PW-M_1x02_P2.50mm_Horizontal
J405: MotorDriver; JST_PH_B5B-PH-K_1x05_P2.00mm_Vertical
R401, R402, R403, R404, R405, R407: 10k; R_0402_1005Metric; LCSC C25744
R406: 3mΩ; R_2010_5025Metric; LCSC C105365
RV401: ch1; Potentiometer_Bourns_TC33X_Vertical; LCSC C719176
RV402: ch2; Potentiometer_Bourns_TC33X_Vertical; LCSC C719176
U401: LM2903PWR; TSSOP-8_4.4x3mm_P0.65mm
U402: INA226; VSSOP-10_3x3mm_P0.5mm; LCSC C49851

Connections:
/ESP32Core/GPIO4/ADC1_CH3: J405.1; also elsewhere on the board
/ESP32Core/GPIO5/ADC1_CH4: J405.2; also elsewhere on the board
/ESP32Core/GPIO6/ADC1_CH5: J405.3; also elsewhere on the board
/ESP32Core/GPIO7/ADC1_CH6: J405.4; also elsewhere on the board
/ESP32Core/GPIO8/ADC1_CH7: R402.2, U401.7 (2OUT); also elsewhere on the board
/ESP32Core/GPIO18: R401.2, U401.1 (1OUT); also elsewhere on the board
/I2C_SCL: U402.2 (A0), U402.5 (SCL); also elsewhere on the board
/I2C_SDA: U402.4 (SDA); also elsewhere on the board
/MotorControl/LiPo_{out}: J404.2 (Pin_1), R406.1, U402.9 (Vin-); also elsewhere on the board
/MotorControl/ch1: J402.3, R403.2, R405.1
/MotorControl/ch2: J403.3, R404.1, R407.1
GND: C401.2, C402.2, C403.2, C404.2, C405.2, C406.2, C407.2, C408.2, J401.1 (Pin_2), J402.2, J403.2, J404.1 (Pin_2), J405.5, R405.2, R407.2, RV401.3, RV402.1, U401.4 (GND), U402.7 (GND); also elsewhere on the board
unnamed: J401.2 (Pin_1), R406.2, U402.8 (Vbus), U402.10 (Vin+)
unnamed: C407.1, R403.1, U401.3 (1IN+)
unnamed: C405.1, RV401.2, U401.2 (1IN-)
unnamed: C408.1, R404.2, U401.5 (2IN+)
unnamed: C406.1, RV402.2, U401.6 (2IN-)
VDD: C401.1, C402.1, C403.1, C404.1, J402.1, J403.1, R401.1, R402.1, RV401.1, RV402.3, U401.8 (VCC), U402.1 (A1), U402.6 (VS); also elsewhere on the board

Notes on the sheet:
PowerMeasure
I2C ADDR : 0x47
Tachometer
MotorDriver

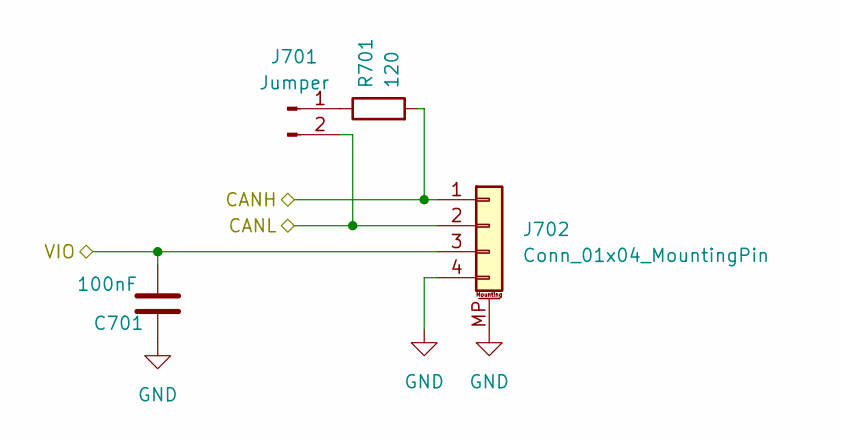
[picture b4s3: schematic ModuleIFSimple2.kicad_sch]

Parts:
C701: 100nF; C_0402_1005Metric; LCSC C1525
J701: Jumper; PinHeader_1x02_P1.27mm_Vertical
J702: Conn_01x04_MountingPin; Grove_4P_L_SMD
R701: 120; R_0402_1005Metric; LCSC C25079

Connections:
/CANH: J702.1, R701.2; also elsewhere on the board
/CANL: J701.2, J702.2; also elsewhere on the board
GND: C701.1, J702.4, J702.MP (MountPin); also elsewhere on the board
unnamed: J701.1, R701.1
VDD: C701.2, J702.3; also elsewhere on the board

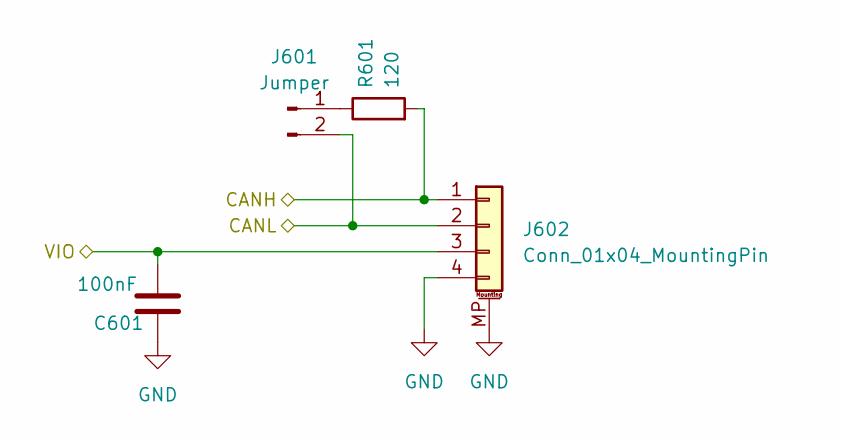
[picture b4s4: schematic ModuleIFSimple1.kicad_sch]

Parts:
C601: 100nF; C_0402_1005Metric; LCSC C1525
J601: Jumper; PinHeader_1x02_P1.27mm_Vertical
J602: Conn_01x04_MountingPin; Grove_4P_L_SMD
R601: 120; R_0402_1005Metric; LCSC C25079

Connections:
/CANH: J602.1, R601.2; also elsewhere on the board
/CANL: J601.2, J602.2; also elsewhere on the board
GND: C601.1, J602.4, J602.MP (MountPin); also elsewhere on the board
unnamed: J601.1, R601.1
VDD: C601.2, J602.3; also elsewhere on the board
